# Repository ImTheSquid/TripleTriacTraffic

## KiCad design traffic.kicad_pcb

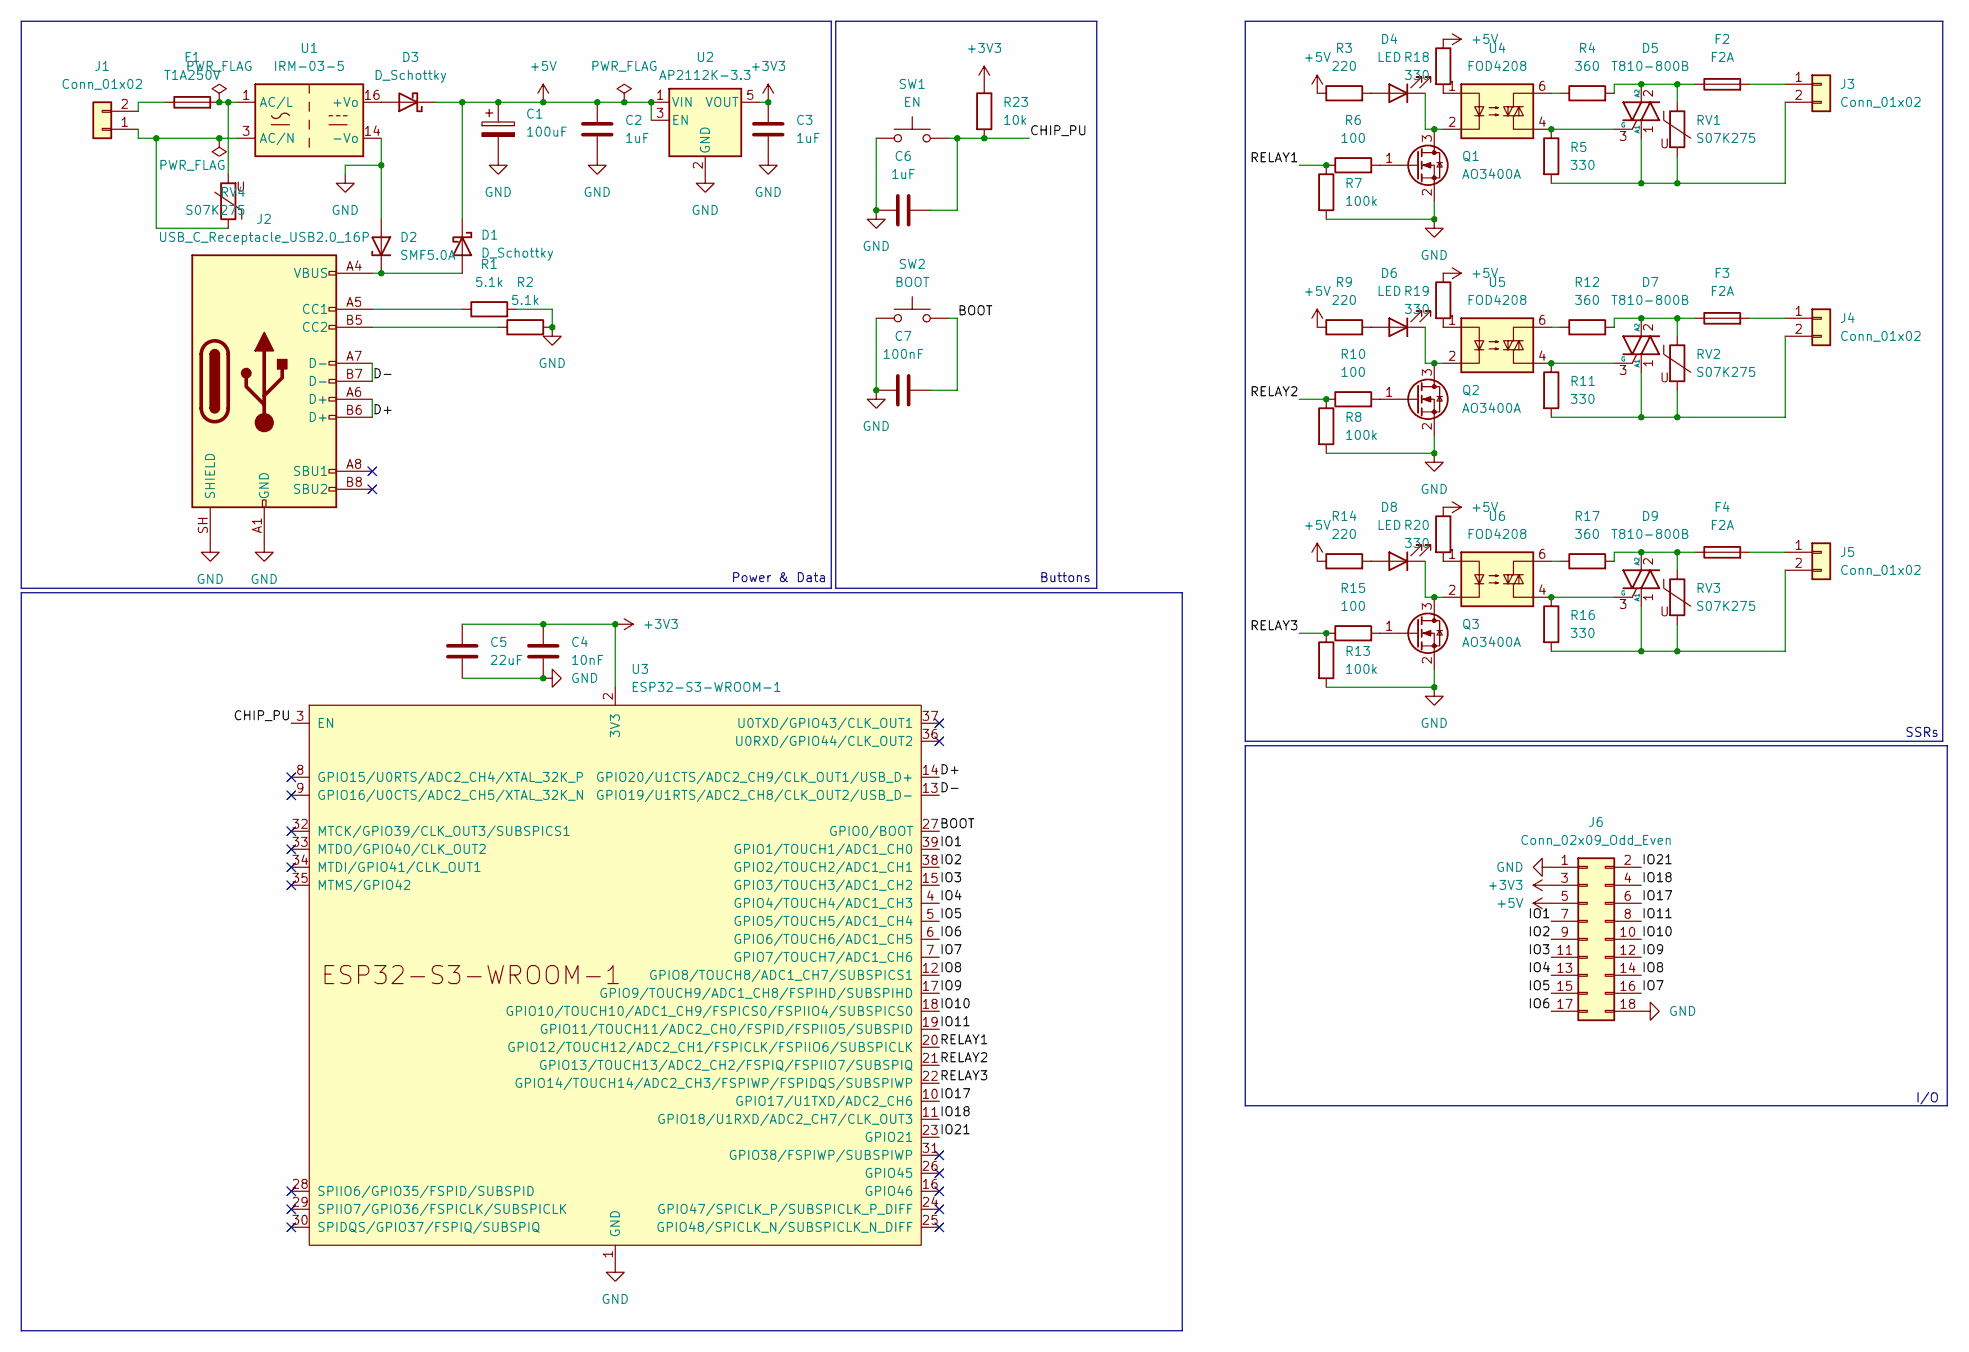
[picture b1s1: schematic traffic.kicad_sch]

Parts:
C1: 100uF; CP_Elec_6.3x7.7
C2, C3, C6: 1uF; C_0402_1005Metric
C4: 10nF; C_0402_1005Metric
C5: 22uF; C_0805_2012Metric
C7: 100nF; C_0402_1005Metric
D1, D3: D_Schottky; D_SOD-123F
D2: SMF5.0A; D_SOD-123F
D4, D6, D8: LED; LED_0402_1005Metric
D5, D7, D9: T810-800B; TO-252-2
F1: T1A250V; Fuseholder_TR5_Littelfuse_No560_No460
F2, F3, F4: F2A; Fuseholder_TR5_Littelfuse_No560_No460
J1, J3, J4, J5: Conn_01x02; TerminalBlock_Phoenix_MKDS-1,5-2-5.08_1x02_P5.08mm_Horizont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
J2: USB_C_Receptacle_USB2.0_16P; USB_C_Receptacle_GCT_USB4105-xx-A_16P_TopMnt_Horizontal
J6: Conn_02x09_Odd_Even; PinHeader_2x09_P2.54mm_Vertical
Q1, Q2, Q3: AO3400A; SOT-23
R1, R2: 5.1k; R_0402_1005Metric
R3, R9, R14: 220; R_0402_1005Metric
R4, R12, R17: 360; R_1206_3216Metric
R5, R11, R16, R18, R19, R20: 330; R_0402_1005Metric
R6, R10, R15: 100; R_0402_1005Metric
R7, R8, R13: 100k; R_0402_1005Metric
R23: 10k; R_0402_1005Metric
RV1, RV2, RV3, RV4: S07K275; RV_Disc_D7mm_W4.5mm_P5mm
SW1: EN; SW_SPST_PTS810
SW2: BOOT; SW_SPST_PTS810
U1: IRM-03-5; Converter_ACDC_MeanWell_IRM-03-xx_THT
U2: AP2112K-3.3; SOT-23-5
U3: ESP32-S3-WROOM-1
U4, U5, U6: FOD4208; SMDIP-6_W7.62mm

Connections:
+3V3: C3.1, C4.2, C5.2, J6.3, R23.1, U2.5 (VOUT), U3.2 (3V3)
+5V: C1.1, C2.1, D1.1 (K), D3.1 (K), J6.5, R3.1, R9.1, R14.1, R18.1, R19.1, R20.1, U2.1 (VIN), U2.3 (EN)
/BOOT: C7.1, SW2.2, U3.27 (GPIO0/BOOT)
/CHIP_PU: C6.1, R23.2, SW1.2, U3.3 (EN)
/D+: J2.A6 (D+), J2.B6 (D+), U3.14 (GPIO20/U1CTS/ADC2_CH9/CLK_OUT1/USB_D+)
/D-: J2.A7 (D-), J2.B7 (D-), U3.13 (GPIO19/U1RTS/ADC2_CH8/CLK_OUT2/USB_D-)
/IO1: J6.7, U3.39 (GPIO1/TOUCH1/ADC1_CH0)
/IO2: J6.9, U3.38 (GPIO2/TOUCH2/ADC1_CH1)
/IO3: J6.11, U3.15 (GPIO3/TOUCH3/ADC1_CH2)
/IO4: J6.13, U3.4 (GPIO4/TOUCH4/ADC1_CH3)
/IO5: J6.15, U3.5 (GPIO5/TOUCH5/ADC1_CH4)
/IO6: J6.17, U3.6 (GPIO6/TOUCH6/ADC1_CH5)
/IO7: J6.16, U3.7 (GPIO7/TOUCH7/ADC1_CH6)
/IO8: J6.14, U3.12 (GPIO8/TOUCH8/ADC1_CH7/SUBSPICS1)
/IO9: J6.12, U3.17 (GPIO9/TOUCH9/ADC1_CH8/FSPIHD/SUBSPIHD)
/IO10: J6.10, U3.18 (GPIO10/TOUCH10/ADC1_CH9/FSPICS0/FSPIIO4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)
/IO11: J6.8, U3.19 (GPIO11/TOUCH11/ADC2_CH0/FSPID/FSPIIO5/S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)
/IO17: J6.6, U3.10 (GPIO17/U1TXD/ADC2_CH6)
/IO18: J6.4, U3.11 (GPIO18/U1RXD/ADC2_CH7/CLK_OUT3)
/IO21: J6.2, U3.23 (GPIO21)
/RELAY1: R6.1, R7.1, U3.20 (GPIO12/TOUCH12/ADC2_CH1/FSPICLK/FSPIIO6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)
/RELAY2: R8.1, R10.1, U3.21 (GPIO13/TOUCH13/ADC2_CH2/FSPIQ/FSPIIO7/S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)
/RELAY3: R13.1, R15.1, U3.22 (GPIO14/TOUCH14/ADC2_CH3/FSPIWP/FSPIDQS/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)
GND: C1.2, C2.2, C3.2, C4.1, C5.1, C6.2, C7.2, D2.2 (A), J2.A1 (GND), J2.A12 (GND), J2.B1 (GND), J2.B12 (GND), J2.SH (SHIELD), J6.1, J6.18, Q1.2 (S), Q2.2 (S), Q3.2 (S), R1.2, R2.2, R7.2, R8.2, R13.2, SW1.1, SW2.1, U1.14 (-Vo), U2.2 (GND), U3.1 (GND), U3.40 (GND), U3.41 (GND)
unnamed: D1.2 (A), D2.1 (K), J2.A4 (VBUS), J2.A9 (VBUS), J2.B4 (VBUS), J2.B9 (VBUS)
unnamed: D3.2 (A), U1.16 (+Vo)
unnamed: D4.2 (A), R3.2
unnamed: D4.1 (K), Q1.3 (D), U4.2
unnamed: D5.1 (A1), J3.2, R5.2, RV1.2
unnamed: D5.2 (A2), F2.1, R4.2, RV1.1
unnamed: D5.3 (G), R5.1, U4.4
unnamed: D6.2 (A), R9.2
unnamed: D6.1 (K), Q2.3 (D), U5.2
unnamed: D7.1 (A1), J4.2, R11.2, RV2.2
unnamed: D7.2 (A2), F3.1, R12.2, RV2.1
unnamed: D7.3 (G), R11.1, U5.4
unnamed: D8.2 (A), R14.2
unnamed: D8.1 (K), Q3.3 (D), U6.2
unnamed: D9.1 (A1), J5.2, R16.2, RV3.2
unnamed: D9.2 (A2), F4.1, R17.2, RV3.1
unnamed: D9.3 (G), R16.1, U6.4
unnamed: J1.1, RV4.1, U1.3 (AC/N)
unnamed: F1.1, J1.2
unnamed: J2.A5 (CC1), R1.1
unnamed: J2.B5 (CC2), R2.1
unnamed: F2.2, J3.1
unnamed: F3.2, J4.1
unnamed: F4.2, J5.1
unnamed: Q1.1 (G), R6.2
unnamed: Q2.1 (G), R10.2
unnamed: Q3.1 (G), R15.2
unnamed: R4.1, U4.6
unnamed: R12.1, U5.6
unnamed: R17.1, U6.6
unnamed: R18.2, U4.1
unnamed: R19.2, U5.1
unnamed: R20.2, U6.1
unnamed: F1.2, RV4.2, U1.1 (AC/L)

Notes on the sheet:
I/O
Power & Data
Buttons
SSRs

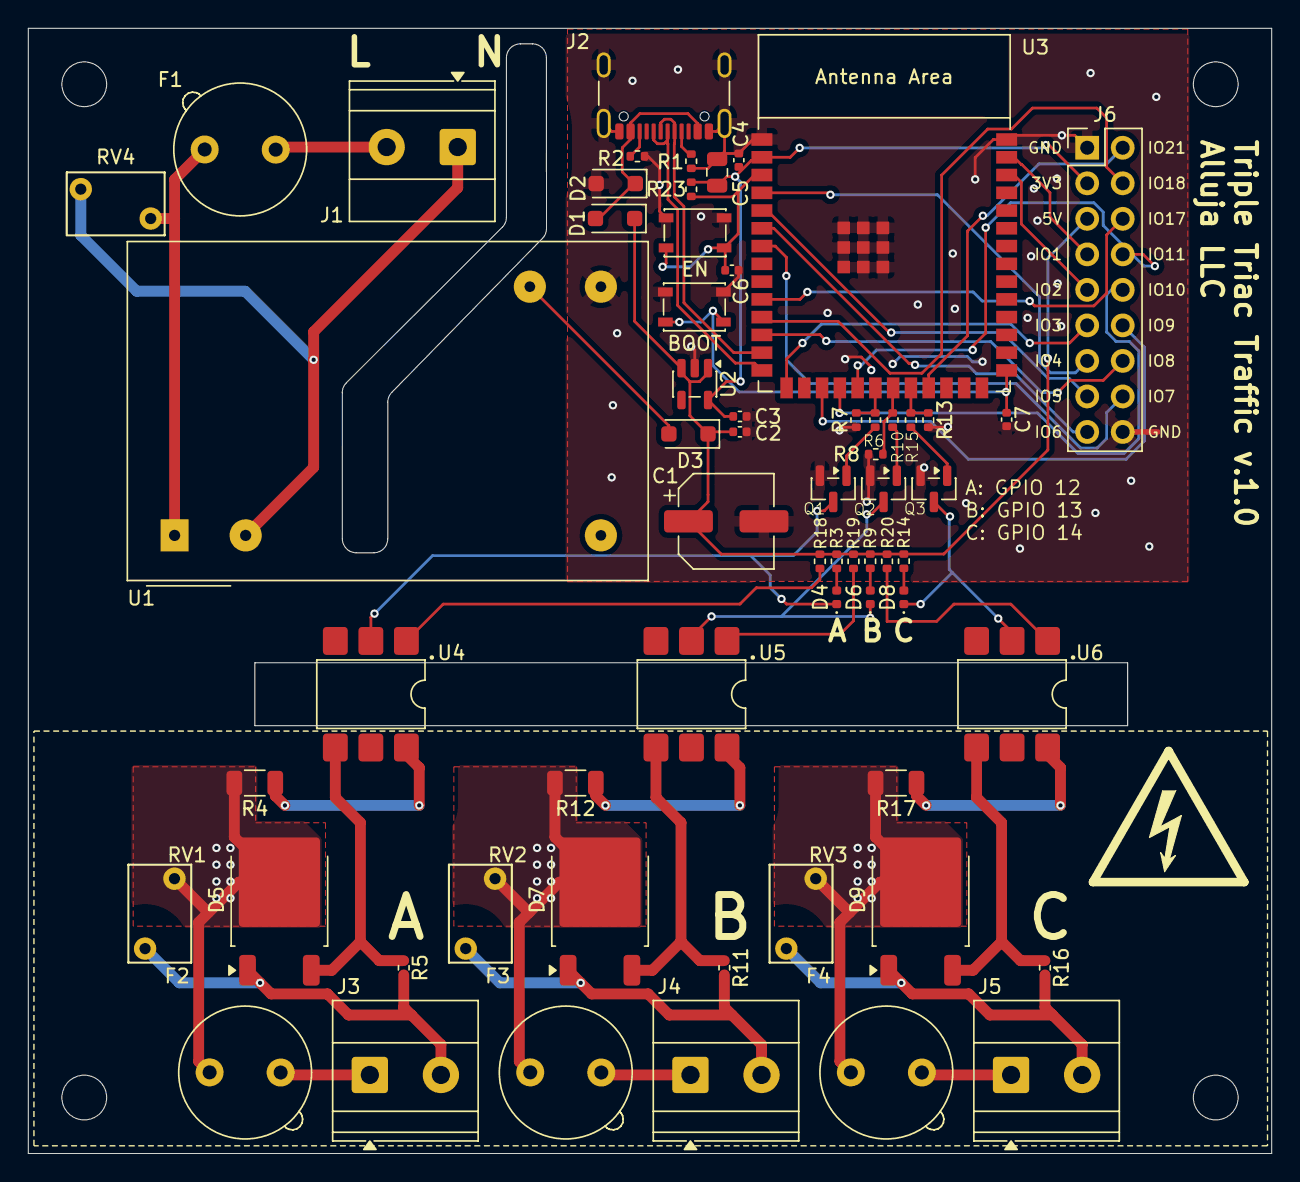
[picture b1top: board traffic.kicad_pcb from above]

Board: 2 copper layers, 88.9 x 80.5 mm, 66 parts (0 on the bottom side), 58 nets.

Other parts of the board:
H1, H2, H3, H4: MountingHole_3.2mm_M3
